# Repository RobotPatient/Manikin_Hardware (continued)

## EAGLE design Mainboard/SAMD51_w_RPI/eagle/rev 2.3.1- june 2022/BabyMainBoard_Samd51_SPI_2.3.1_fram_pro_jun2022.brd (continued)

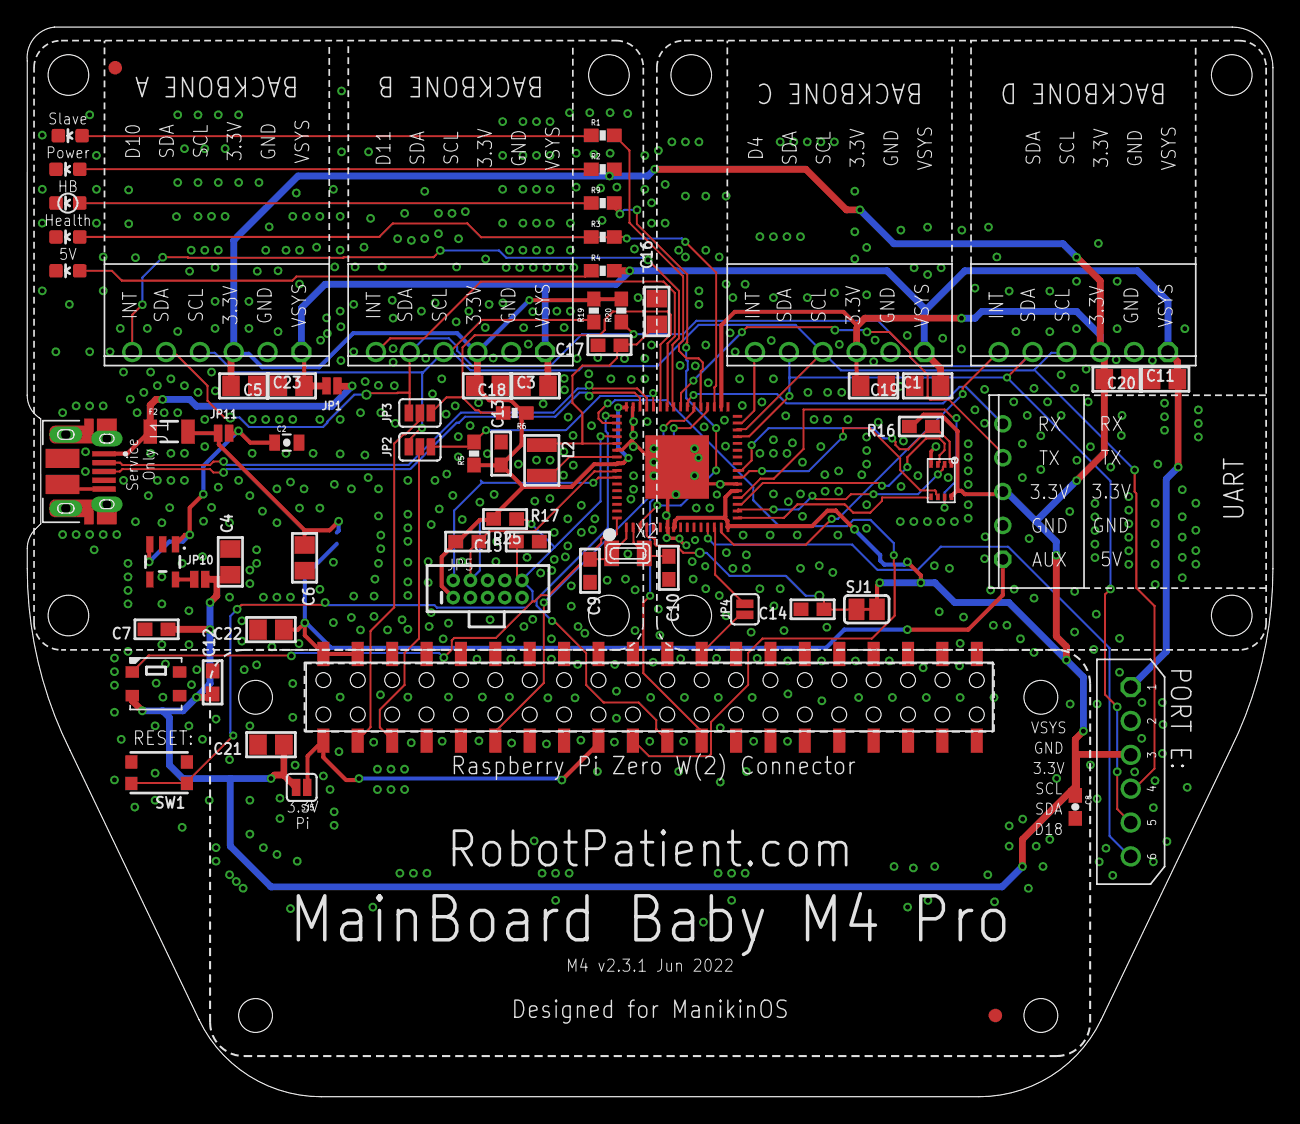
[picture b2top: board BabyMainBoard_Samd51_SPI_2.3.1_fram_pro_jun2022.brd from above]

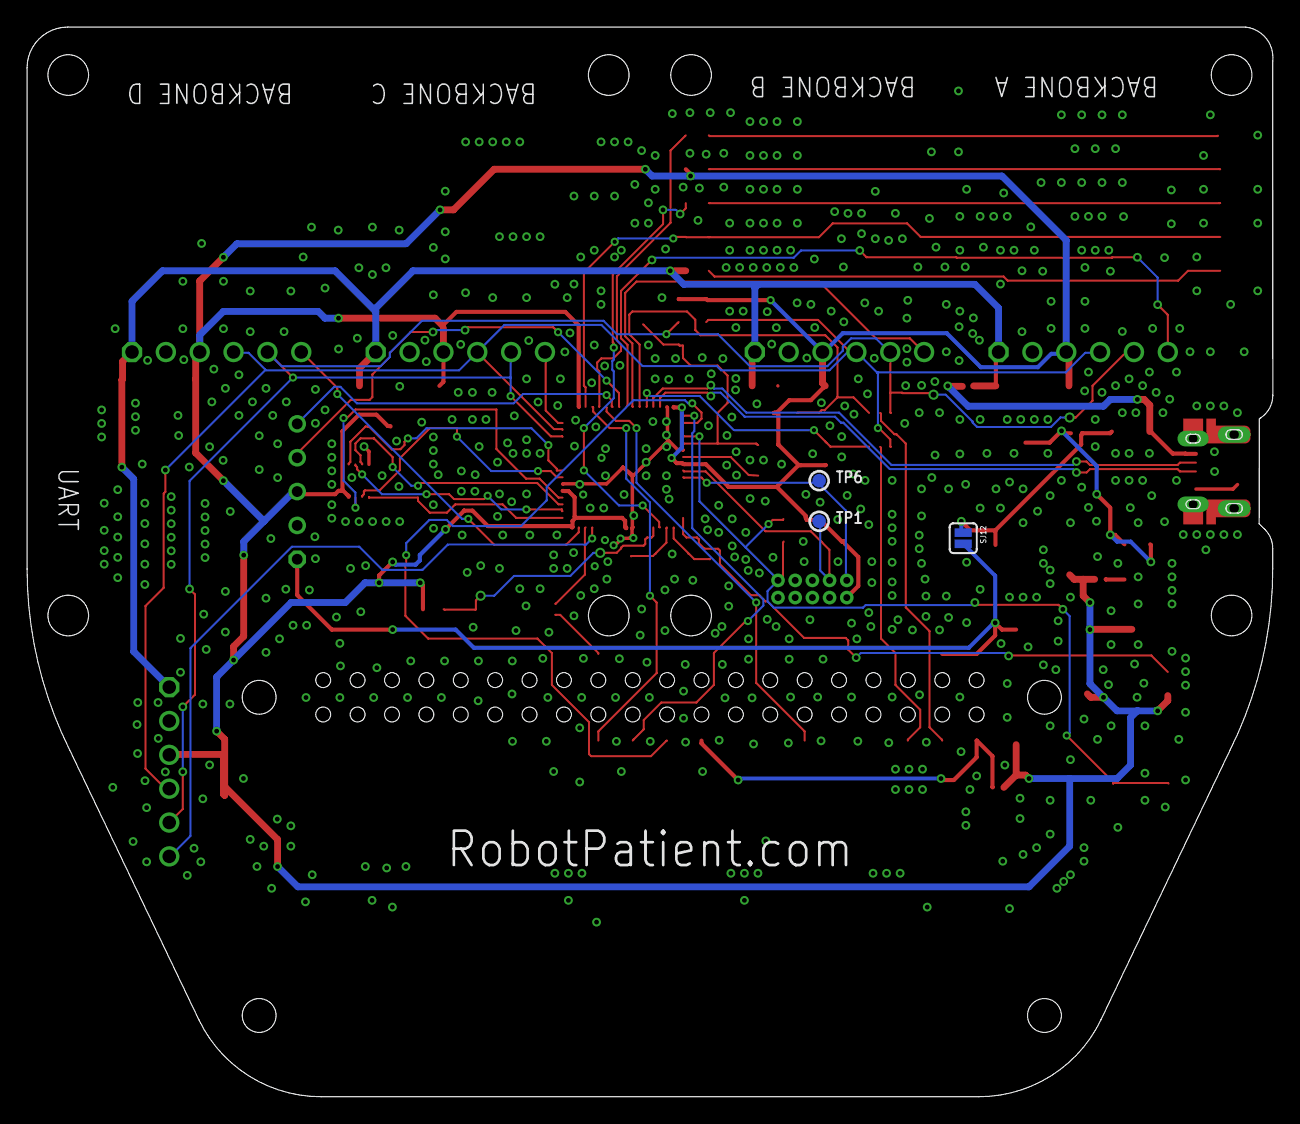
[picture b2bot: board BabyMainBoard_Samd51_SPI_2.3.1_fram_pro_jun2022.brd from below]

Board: 2 copper layers, 92.0 x 79.0 mm, 72 parts (3 on the bottom side), 52 nets.

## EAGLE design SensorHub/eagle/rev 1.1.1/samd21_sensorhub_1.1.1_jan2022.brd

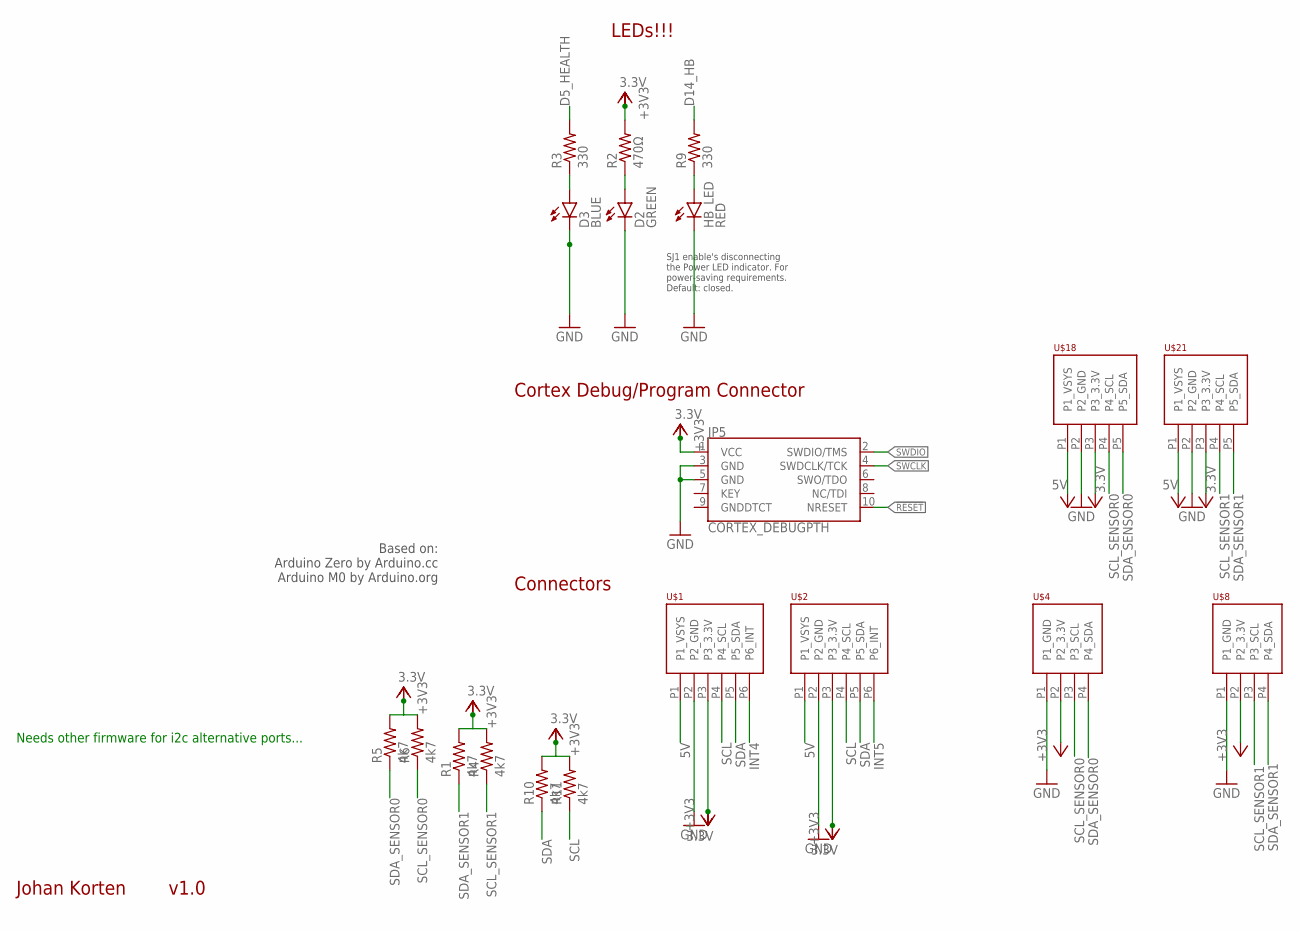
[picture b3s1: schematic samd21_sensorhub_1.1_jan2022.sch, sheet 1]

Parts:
D2: GREEN; LED-0603
D3: BLUE; LED-0603
HB_LED: RED; LED-0603
JP5: CORTEX_DEBUGPTH; 2X5-PTH-1.27MM
R1, R4, R5, R6, R10, R11: 4k7; 0603-RES
R2: 470Ω; 0603-RES
R3, R9: 330; 0603-RES
U$1, U$2: PHOENIX_PTSM_M6_TH_I2CPPANGLE; PTSM_M6_THRHOLE
U$4, U$8: PHOENIX_PTSM_M4_THANGLE; PTSM_M4_TH
U$18, U$21: PHOENIX_PTSM_M5_TH_I2C++; PTSM_M5_THRHOLE

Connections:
3.3V: JP5.1 (VCC), R1.2, R2.2, R4.2, R5.2, R6.2, R10.2, R11.2, U$1.P3 (P3_3.3V), U$2.P3 (P3_3.3V), U$4.P2 (P2_3.3V), U$8.P2 (P2_3.3V), U$18.P3 (P3_3.3V), U$21.P3 (P3_3.3V); also elsewhere on the board
5V: U$1.P1 (P1_VSYS), U$2.P1 (P1_VSYS), U$18.P1 (P1_VSYS), U$21.P1 (P1_VSYS); also elsewhere on the board
!RESET: JP5.10 (NRESET); also elsewhere on the board
D5_HEALTH: R3.2; also elsewhere on the board
D5_HEALTH_LED: D3.A, R3.1
D14_HB: R9.2; also elsewhere on the board
D14_HB_LED: HB_LED.A, R9.1
GND: D2.C, D3.C, HB_LED.C, JP5.3 (GND), JP5.5 (GND), U$1.P2 (P2_GND), U$2.P2 (P2_GND), U$4.P1 (P1_GND), U$8.P1 (P1_GND), U$18.P2 (P2_GND), U$21.P2 (P2_GND); also elsewhere on the board
INT4: U$1.P6 (P6_INT); also elsewhere on the board
INT5: U$2.P6 (P6_INT); also elsewhere on the board
unnamed: D2.A, R2.1
SCL: R11.1, U$1.P4 (P4_SCL), U$2.P4 (P4_SCL); also elsewhere on the board
SCL_SENSOR0: R6.1, U$4.P3 (P3_SCL), U$18.P4 (P4_SCL); also elsewhere on the board
SCL_SENSOR1: R4.1, U$8.P3 (P3_SCL), U$21.P4 (P4_SCL); also elsewhere on the board
SDA: R10.1, U$1.P5 (P5_SDA), U$2.P5 (P5_SDA); also elsewhere on the board
SDA_SENSOR0: R5.1, U$4.P4 (P4_SDA), U$18.P5 (P5_SDA); also elsewhere on the board
SDA_SENSOR1: R1.1, U$8.P4 (P4_SDA), U$21.P5 (P5_SDA); also elsewhere on the board
SWCLK: JP5.4 (SWDCLK/TCK); also elsewhere on the board
SWDIO: JP5.2 (SWDIO/TMS); also elsewhere on the board

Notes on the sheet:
LEDs!!!
Cortex Debug/Program Connector
Connectors
Johan Korten
v1.0
SJ1 enable's disconnecting the Power LED indicator. For power-saving requirements. Default: closed.
Based on: Arduino Zero by Arduino.cc Arduino M0 by Arduino.org
Needs other firmware for i2c alternative ports...

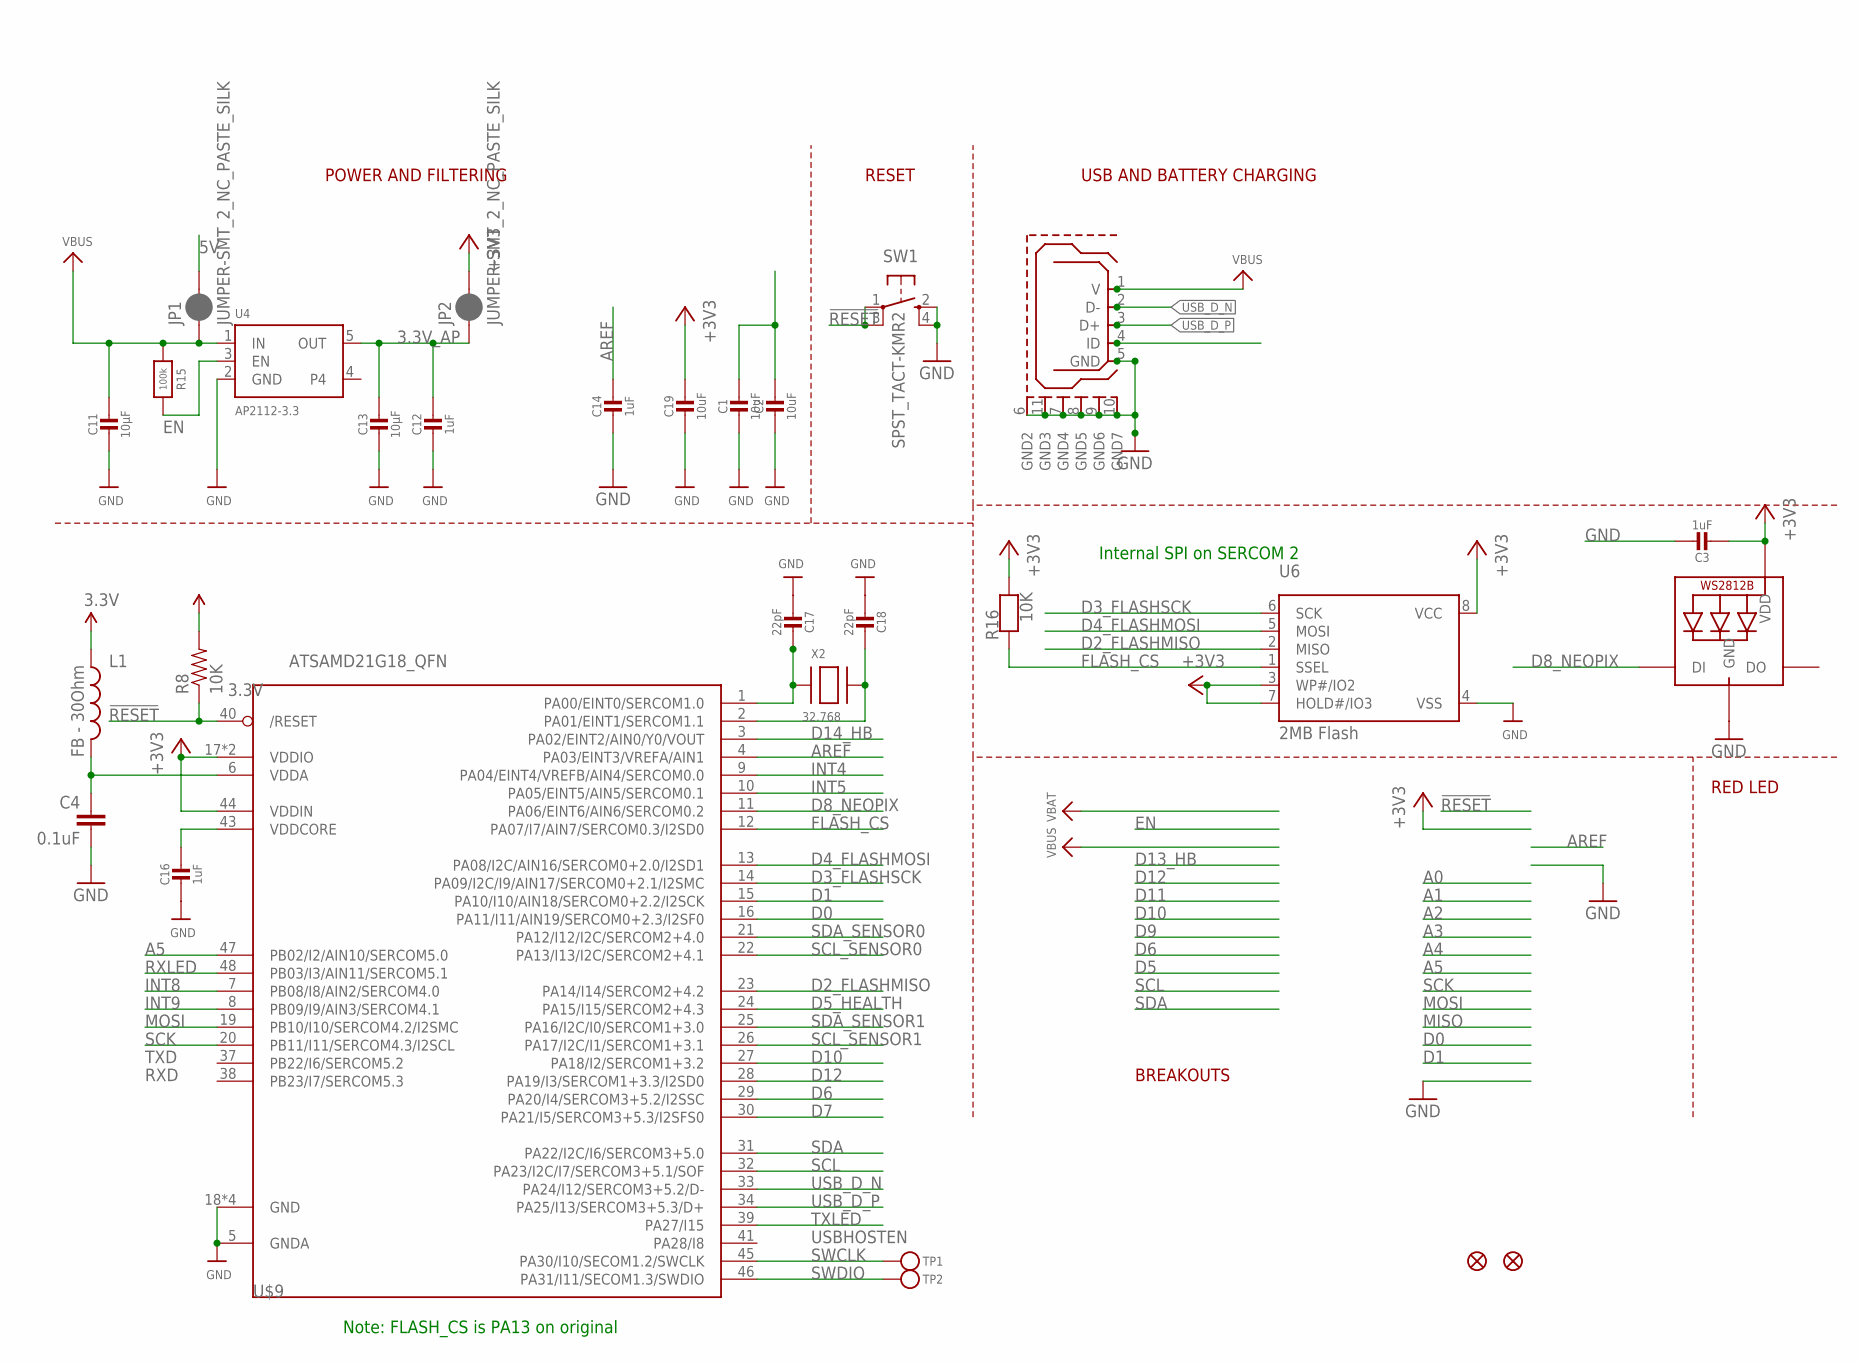
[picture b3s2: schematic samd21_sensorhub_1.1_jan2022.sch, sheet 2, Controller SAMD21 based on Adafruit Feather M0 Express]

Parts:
C1, C2, C19: 10uF; 0805-NO
C3, C12, C14, C16: 1uF; 0603-NO
C4: 0.1uF; 0402-CAP
C11, C13: 10µF; 0805-NO
C17, C18: 22pF; 0603-NO
JP1, JP2: JUMPER-SMT_2_NC_PASTE_SILK; SMT-JUMPER_2_NC_PASTE_SILK
L1: FB - 30Ohm; 0603
LED1: WS2812B3535; LED3535
R8: 10K; 0603-RES
R15: 100k; 0603-NO
R16: 10K; 0603-NO
SW1: SPST_TACT-KMR2; KMR2
TP1, TP2: TESTPOINTROUND1.5MM; TESTPOINT_ROUND_1.5MM
U4: AP2112-3.3; SOT23-5
U6: 2MB Flash; SOIC8_208MIL
U$6: USB_MICROB; USB_MICROB_PACKAGE
U$9: ATSAMD21G18_QFN; TQFN48_7MM
U$34, U$35: FIDUCIAL""; FIDUCIAL_1MM
X2: 32.768; XTAL3215

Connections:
3.3V: C3.2, C19.1, JP2.2, L1.1, LED1.2 (VDD), R8.2, R16.2, U6.3 (WP#/IO2), U6.7 (HOLD#/IO3), U6.8 (VCC), U$9.17 (VDDIO), U$9.36 (VDDIO), U$9.44 (VDDIN); also elsewhere on the board
3.3V_AP: C12.1, C13.1, JP2.1, U4.5 (OUT)
5V: C1.1, C2.1, JP1.2; also elsewhere on the board
!RESET: R8.1, SW1.1, SW1.3 (P1), U$9.40 (/RESET); also elsewhere on the board
A5: U$9.47 (PB02/I2/AIN10/SERCOM5.0)
AREF: C14.1, U$9.4 (PA03/EINT3/VREFA/AIN1)
D0: U$9.16 (PA11/I11/AIN19/SERCOM0+2.3/I2SF0)
D1: U$9.15 (PA10/I10/AIN18/SERCOM0+2.2/I2SCK)
D2_FLASHMISO: U6.2 (MISO), U$9.23 (PA14/I14/SERCOM2+4.2)
D3_FLASHSCK: U6.6 (SCK), U$9.14 (PA09/I2C/I9/AIN17/SERCOM0+2.1/I2SMC)
D4_FLASHMOSI: U6.5 (MOSI), U$9.13 (PA08/I2C/AIN16/SERCOM0+2.0/I2SD1)
D5_HEALTH: U$9.24 (PA15/I15/SERCOM2+4.3); also elsewhere on the board
D6: U$9.29 (PA20/I4/SERCOM3+5.2/I2SSC)
D7: U$9.30 (PA21/I5/SERCOM3+5.3/I2SFS0)
D8_NEOPIX: LED1.1 (DI), U$9.11 (PA06/EINT6/AIN6/SERCOM0.2)
D10: U$9.27 (PA18/I2/SERCOM1+3.2)
D12: U$9.28 (PA19/I3/SERCOM1+3.3/I2SD0)
D14_HB: U$9.3 (PA02/EINT2/AIN0/Y0/VOUT); also elsewhere on the board
EN: R15.2, U4.3 (EN)
FLASH_CS: R16.1, U6.1 (SSEL), U$9.12 (PA07/I7/AIN7/SERCOM0.3/I2SD0)
GND: C1.2, C2.2, C3.1, C4.2, C11.2, C12.2, C13.2, C14.2, C16.2, C17.2, C18.2, C19.2, LED1.4 (GND), SW1.2 (S), SW1.4 (S1), U4.2 (GND), U6.4 (VSS), U$6.5 (GND), U$6.6 (GND2), U$6.7 (GND4), U$6.8 (GND5), U$6.9 (GND6), U$6.10 (GND7), U$6.11 (GND3), U$9.5 (GNDA), U$9.18 (GND), U$9.35 (GND), U$9.42 (GND), U$9.THERMAL (GND); also elsewhere on the board
INT4: U$9.9 (PA04/EINT4/VREFB/AIN4/SERCOM0.0); also elsewhere on the board
INT5: U$9.10 (PA05/EINT5/AIN5/SERCOM0.1); also elsewhere on the board
INT8: U$9.7 (PB08/I8/AIN2/SERCOM4.0)
INT9: U$9.8 (PB09/I9/AIN3/SERCOM4.1)
MOSI: U$9.19 (PB10/I10/SERCOM4.2/I2SMC)
unnamed: C17.1, U$9.1 (PA00/EINT0/SERCOM1.0), X2.P$1
unnamed: C18.1, U$9.2 (PA01/EINT1/SERCOM1.1), X2.P$2
RXLED: U$9.48 (PB03/I3/AIN11/SERCOM5.1)
SCK: U$9.20 (PB11/I11/SERCOM4.3/I2SCL)
SCL: U$9.32 (PA23/I2C/I7/SERCOM3+5.1/SOF); also elsewhere on the board
SCL_SENSOR0: U$9.22 (PA13/I13/I2C/SERCOM2+4.1); also elsewhere on the board
SCL_SENSOR1: U$9.26 (PA17/I2C/I1/SERCOM1+3.1); also elsewhere on the board
SDA: U$9.31 (PA22/I2C/I6/SERCOM3+5.0); also elsewhere on the board
SDA_SENSOR0: U$9.21 (PA12/I12/I2C/SERCOM2+4.0); also elsewhere on the board
SDA_SENSOR1: U$9.25 (PA16/I2C/I0/SERCOM1+3.0); also elsewhere on the board
SWCLK: TP1.P$1, U$9.45 (PA30/I10/SECOM1.2/SWCLK); also elsewhere on the board
SWDIO: TP2.P$1, U$9.46 (PA31/I11/SECOM1.3/SWDIO); also elsewhere on the board
TXLED: U$9.39 (PA27/I15)
USB_D_N: U$6.2 (D-), U$9.33 (PA24/I12/SERCOM3+5.2/D-); also elsewhere on the board
USB_D_P: U$6.3 (D+), U$9.34 (PA25/I13/SERCOM3+5.3/D+); also elsewhere on the board
VBUS: C11.1, JP1.1, R15.1, U4.1 (IN), U$6.1 (V); also elsewhere on the board
VDDANA: C4.1, L1.2, U$9.6 (VDDA)
VDDCORE1: C16.1, U$9.43 (VDDCORE)

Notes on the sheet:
POWER AND FILTERING
RESET
USBHOSTEN
TXD
RXD
USB AND BATTERY CHARGING
BREAKOUTS
RED LED
Internal SPI on SERCOM 2
Note: FLASH_CS is PA13 on original

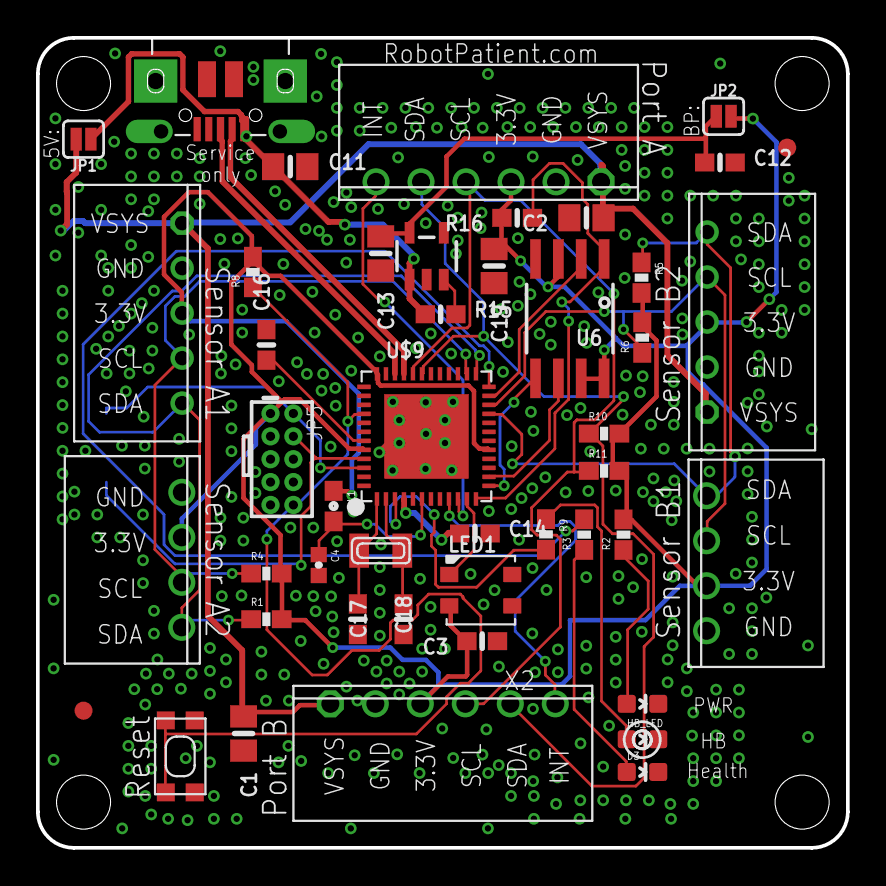
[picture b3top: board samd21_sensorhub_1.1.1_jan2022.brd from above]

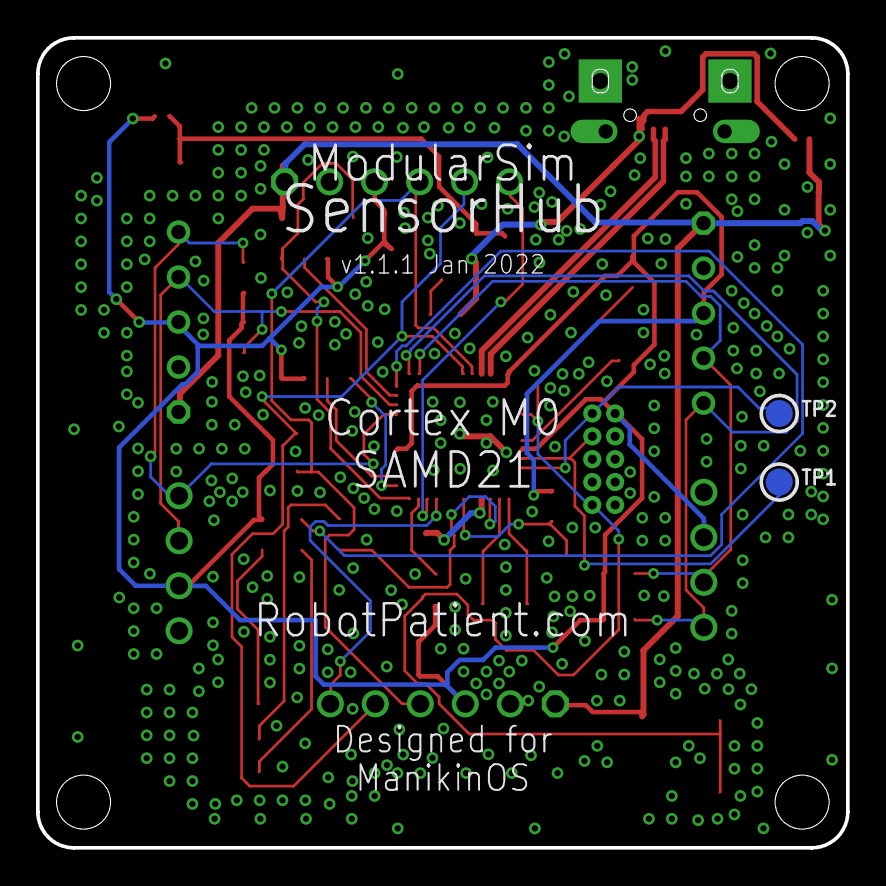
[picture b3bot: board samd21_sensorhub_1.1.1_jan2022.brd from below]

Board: 2 copper layers, 45.0 x 45.0 mm, 48 parts (2 on the bottom side), 34 nets.

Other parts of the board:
X3: microUSB; 4UCONN_20329_V2

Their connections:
GND: X3.BASE@1, X3.BASE@2, X3.GND, X3.SPRT@1, X3.SPRT@2, X3.SPRT@3, X3.SPRT@4; also elsewhere on the board
USB_D_N: X3.D-; also elsewhere on the board
USB_D_P: X3.D+; also elsewhere on the board
VBUS: X3.VBUS; also elsewhere on the board

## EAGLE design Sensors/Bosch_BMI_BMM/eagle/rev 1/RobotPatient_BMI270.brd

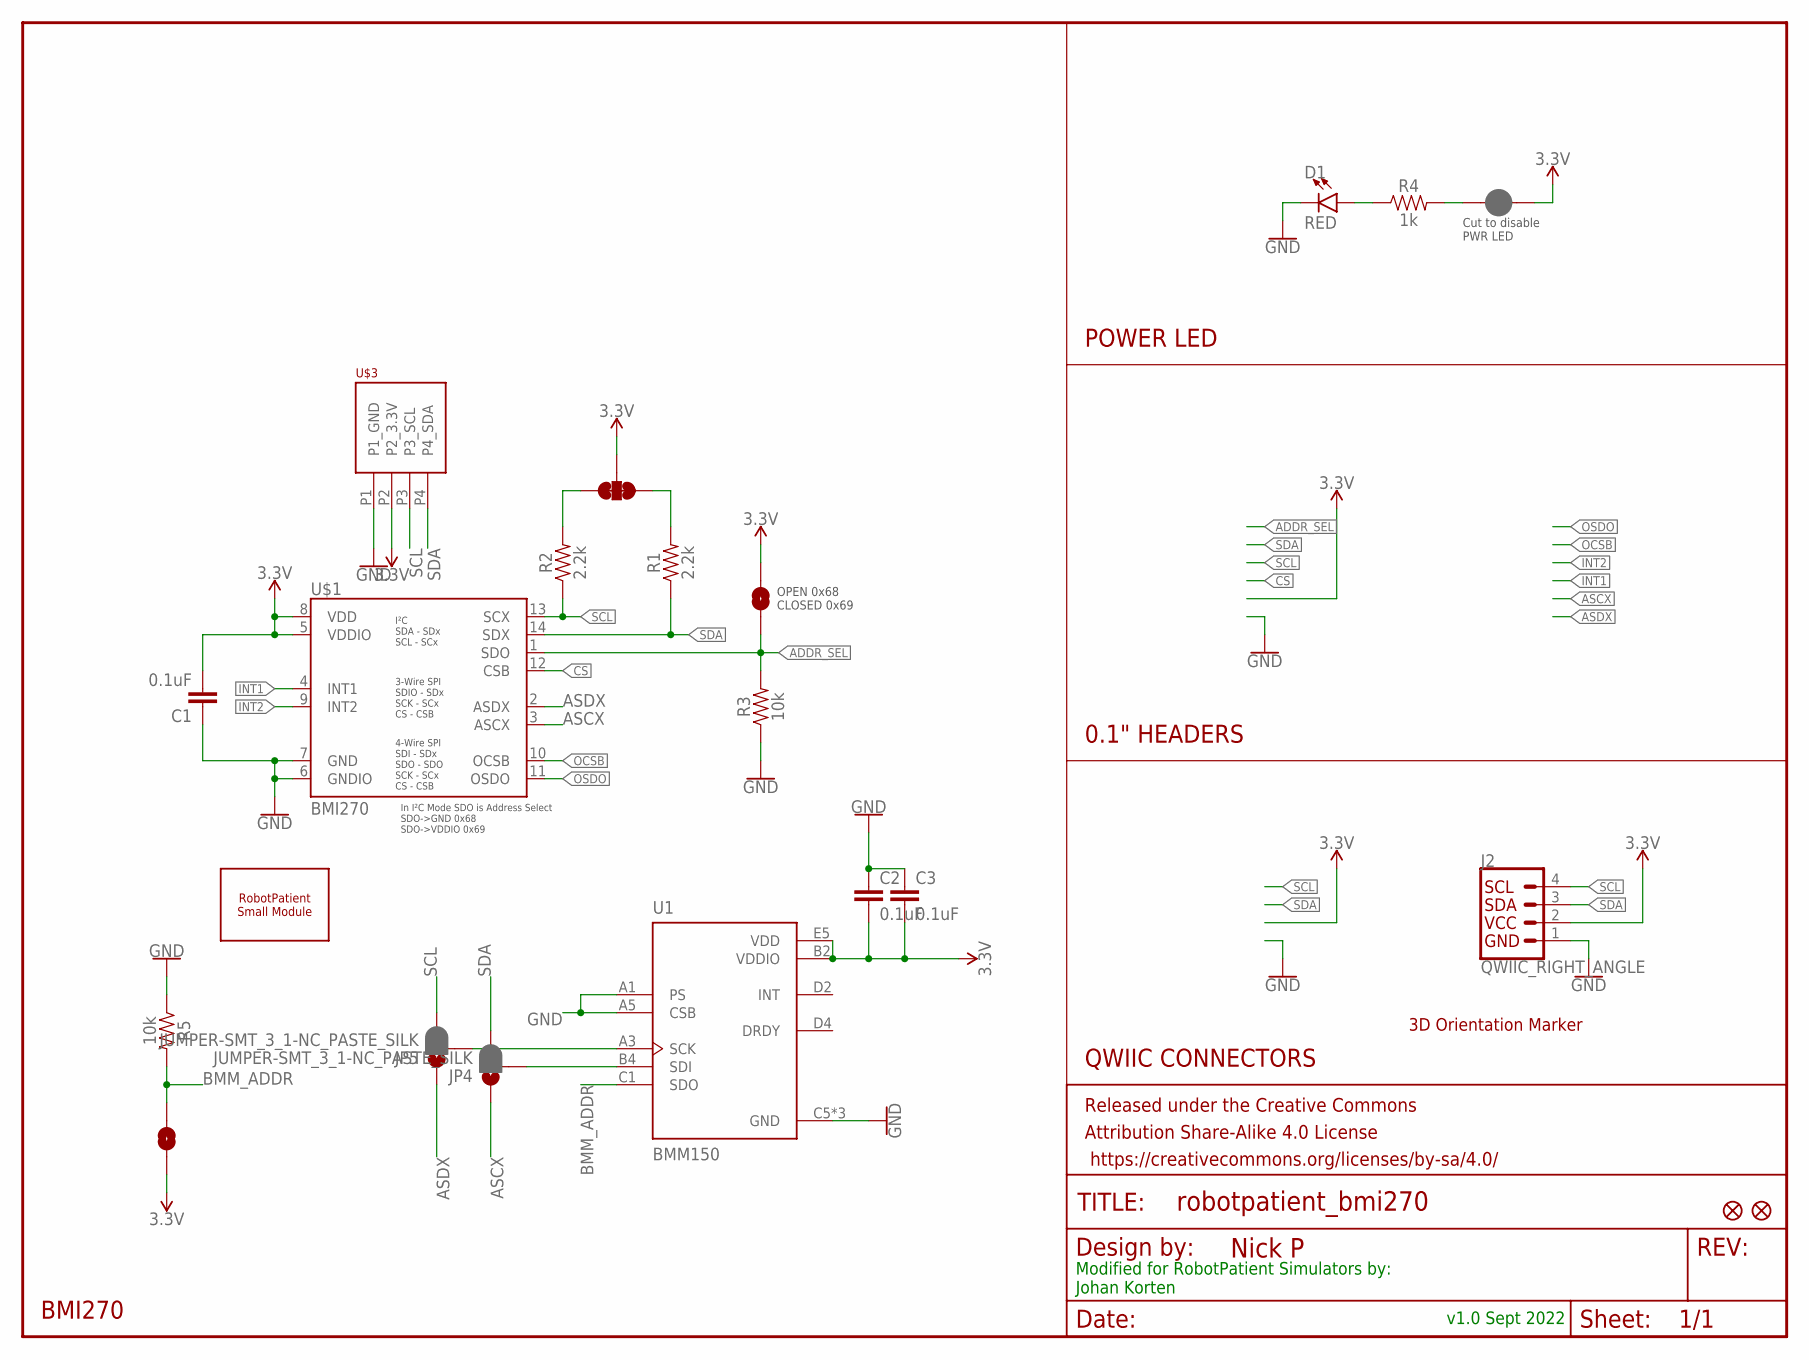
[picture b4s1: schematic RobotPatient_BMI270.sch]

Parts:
C1, C2, C3: 0.1uF; 0603
D1: RED; LED-0603
FD1, FD2: FIDUCIAL1X2; FIDUCIAL-1X2
FRAME1: FRAME-LETTERNO_PACKAGE; DUMMY
J2: QWIIC_RIGHT_ANGLE; JST04_1MM_RA
JP1: JUMPER-SMT_3_2-NC_TRACE_SILK; SMT-JUMPER_3_2-NC_TRACE_SILK
JP2, JP6: JUMPER-SMT_2_NO_SILK; SMT-JUMPER_2_NO_SILK
JP3: JUMPER-SMT_2_NC_PASTE_SILK; SMT-JUMPER_2_NC_PASTE_SILK
JP4, JP5: JUMPER-SMT_3_1-NC_PASTE_SILK; SMT-JUMPER_3_1-NC_PASTE_SILK
R1, R2: 2.2k; 0603
R3, R5: 10k; 0603
R4: 1k; 0603
U1: BMM150; XDCR_BMM150
U$1: BMI270
U$2: 3D_MARKER
U$3: PHOENIX_PTSM_M4_THANGLE; PTSM_M4_TH
U$40: ROBOTPATIENT_SMALL_MODULEBOARD; RP_SMALL_SENSOR_OUTLINE

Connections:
3.3V: C1.2, C2.2, C3.2, J2.2, JP1.2, JP2.2, JP3.2, JP6.2, U1.B2 (VDDIO), U1.E5 (VDD), U$1.5 (VDDIO), U$1.8 (VDD), U$3.P2 (P2_3.3V)
ADDR_SEL: JP2.1, R3.2, U$1.1 (SDO)
ASCX: JP4.1, U$1.3 (ASCX)
ASDX: JP5.1, U$1.2 (ASDX)
BMM_ADDR: JP6.1, R5.2, U1.C1 (SDO)
CS: U$1.12 (CSB)
GND: C1.1, C2.1, C3.1, D1.C, J2.1, R3.1, R5.1, U1.A1 (PS), U1.A5 (CSB), U1.C5 (GND), U1.E1 (GND), U1.E3 (GND), U$1.6 (GNDIO), U$1.7 (GND), U$3.P1 (P1_GND)
INT1: U$1.4 (INT1)
INT2: U$1.9 (INT2)
unnamed: JP1.1, R1.2
unnamed: JP1.3, R2.2
unnamed: JP3.1, R4.2
unnamed: D1.A, R4.1
unnamed: JP4.2, U1.B4 (SDI)
unnamed: JP5.2, U1.A3 (SCK)
OCSB: U$1.10 (OCSB)
OSDO: U$1.11 (OSDO)
SCL: J2.4, JP5.3, R2.1, U$1.13 (SCX), U$3.P3 (P3_SCL)
SDA: J2.3, JP4.3, R1.1, U$1.14 (SDX), U$3.P4 (P4_SDA)

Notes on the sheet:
OPEN 0x68 CLOSED 0x69
BMI270
Cut to disable PWR LED
POWER LED
0.1" HEADERS
QWIIC CONNECTORS
Modified for RobotPatient Simulators by: Johan Korten

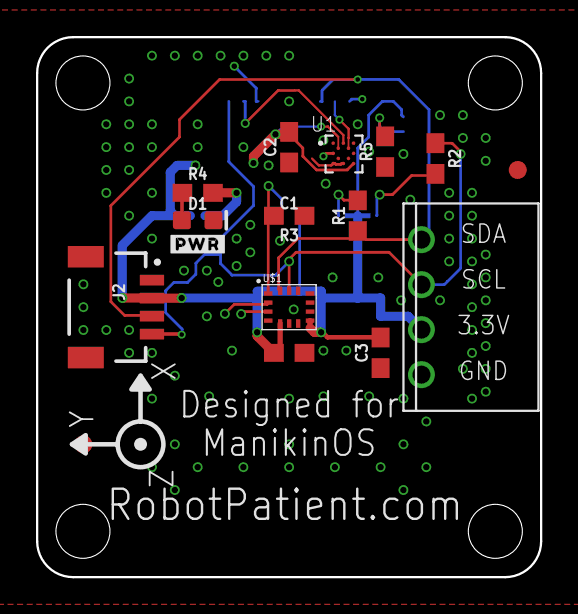
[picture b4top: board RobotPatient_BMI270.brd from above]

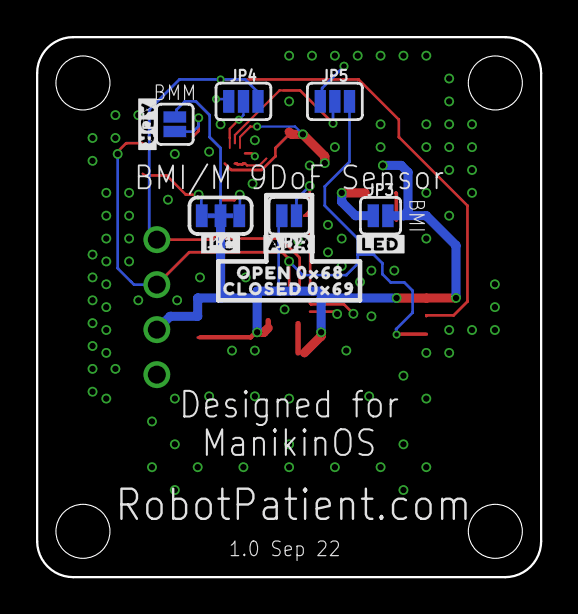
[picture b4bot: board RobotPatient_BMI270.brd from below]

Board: 4 copper layers, 28.0 x 30.0 mm, 31 parts (12 on the bottom side), 14 nets.

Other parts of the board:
U$4, U$23: #ADR#2713
U$18: #PWR#2711
U$21: #I�C#2714
U$22: #LED#2712
U$24: OPEN_0X682714
U$25: CLOSED_0X692714

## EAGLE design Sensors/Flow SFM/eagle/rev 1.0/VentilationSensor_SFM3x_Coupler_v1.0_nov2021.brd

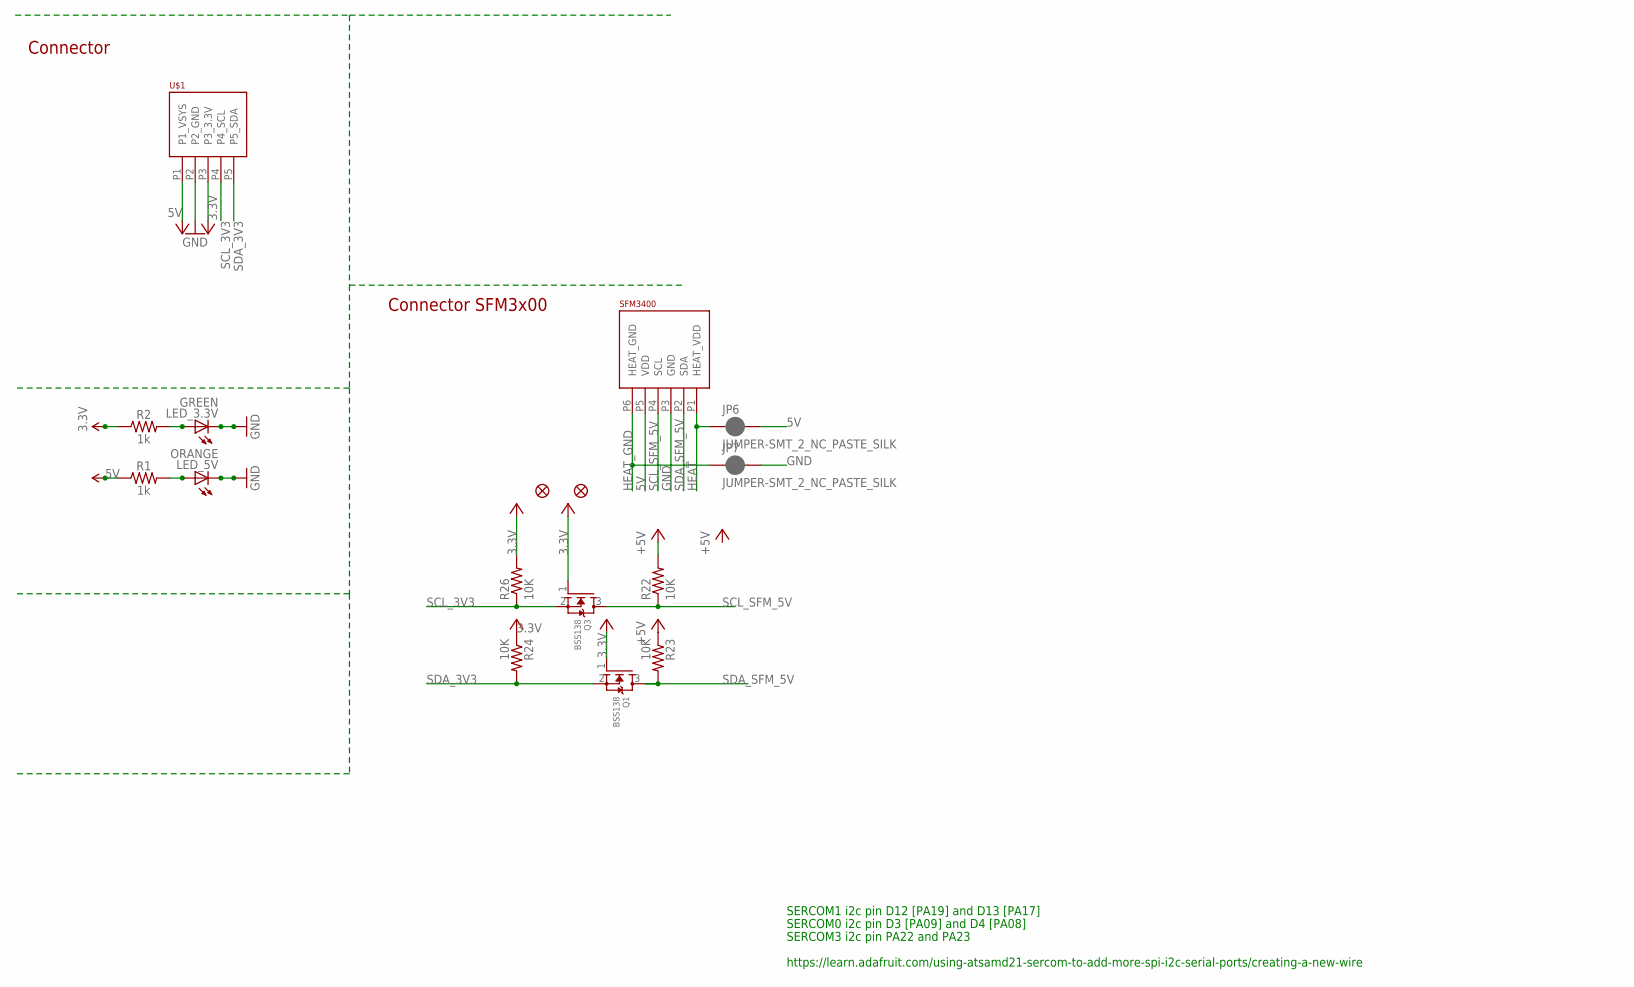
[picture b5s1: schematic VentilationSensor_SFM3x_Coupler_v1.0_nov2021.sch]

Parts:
FD1, FD2: FIDUCIAL1X2; FIDUCIAL-1X2
JP6, JP7: JUMPER-SMT_2_NC_PASTE_SILK; SMT-JUMPER_2_NC_PASTE_SILK
LED_3.3V: GREEN; LED-0603
LED_5V: ORANGE; LED-0603
Q1, Q3: BSS138; SOT23
R1, R2: 1k; 0603
R22, R23, R24, R26: 10K; R0805
SFM3400: SFMXX00
U$1: PHOENIX_PTSM_M5_TH_I2C++; PTSM_M5_THRHOLE

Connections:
3.3V: Q1.1 (G), Q3.1 (G), R2.1, R24.1, R26.2, U$1.P3 (P3_3.3V)
5V: JP6.2, R1.1, R22.2, R23.1, SFM3400.P5 (VDD), U$1.P1 (P1_VSYS)
GND: JP7.2, LED_3.3V.C, LED_5V.C, SFM3400.P3 (GND), U$1.P2 (P2_GND)
HEAT: JP6.1, SFM3400.P1 (HEAT_VDD)
HEAT_GND: JP7.1, SFM3400.P6 (HEAT_GND)
unnamed: LED_5V.A, R1.2
unnamed: LED_3.3V.A, R2.2
SCL_3V3: Q3.2 (S), R26.1, U$1.P4 (P4_SCL)
SCL_SFM_5V: Q3.3 (D), R22.1, SFM3400.P4 (SCL)
SDA_3V3: Q1.2 (S), R24.2, U$1.P5 (P5_SDA)
SDA_SFM_5V: Q1.3 (D), R23.2, SFM3400.P2 (SDA)

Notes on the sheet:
SERCOM1 i2c pin D12 [PA19] and D13 [PA17]
https://learn.adafruit.com/using-atsamd21-sercom-to-add-more-spi-i2c-serial-ports/creating-a-new-wire
SERCOM0 i2c pin D3 [PA09] and D4 [PA08]
SERCOM3 i2c pin PA22 and PA23
Connector SFM3x00
Connector

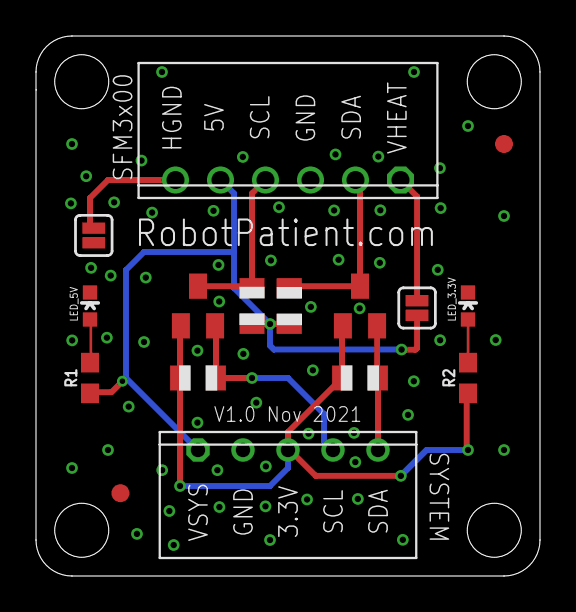
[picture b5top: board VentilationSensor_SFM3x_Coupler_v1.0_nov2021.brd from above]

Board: 2 copper layers, 28.0 x 30.0 mm, 16 parts (0 on the bottom side), 11 nets.

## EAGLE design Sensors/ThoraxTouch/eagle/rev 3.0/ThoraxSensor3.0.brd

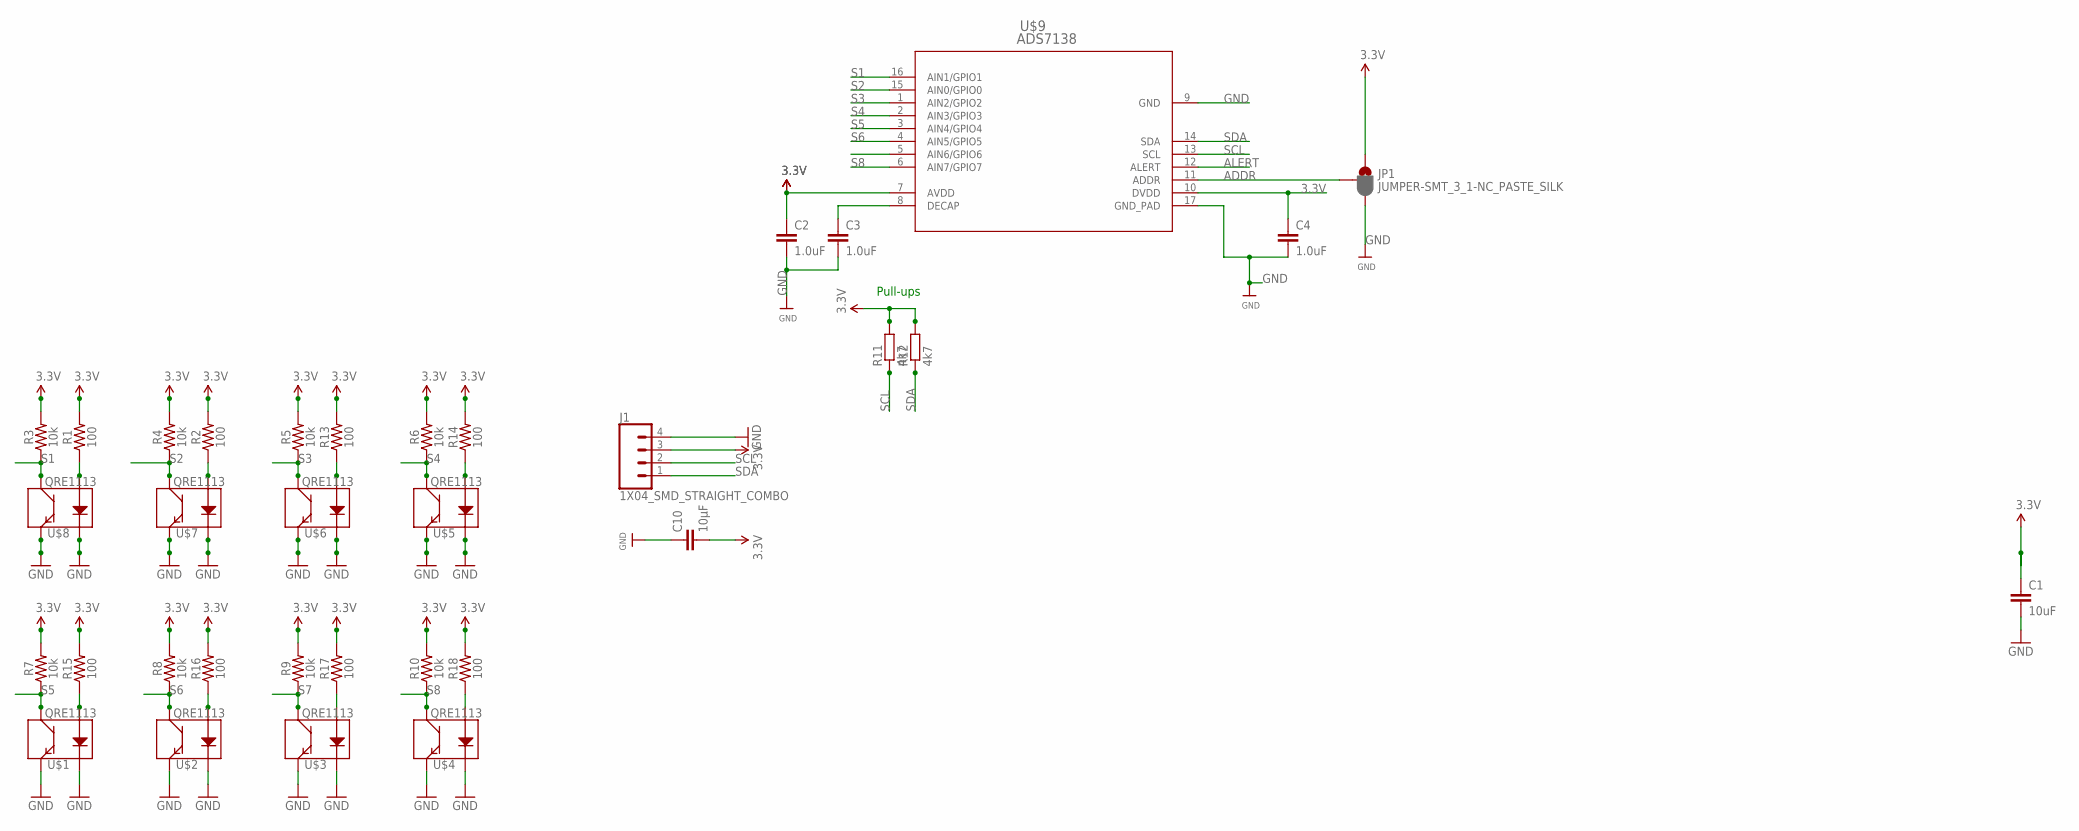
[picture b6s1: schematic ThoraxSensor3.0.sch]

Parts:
C1: 10uF; 0805
C2, C3, C4: 1.0uF; 0603
C10: 10µF; C0805
J1: 1X04_SMD_STRAIGHT_COMBO; 1X04_SMD_VERTICAL_COMBO
JP1: JUMPER-SMT_3_1-NC_PASTE_SILK; SMT-JUMPER_3_1-NC_PASTE_SILK
R1, R2, R13, R14, R15, R16, R17, R18: 100; 0603
R3, R4, R5, R6, R7, R8, R9, R10: 10k; 0603
R11, R12: 4k7; R0603
U$1, U$2, U$3, U$4, U$5, U$6, U$7, U$8: QRE1113
U$9: ADS7138; QFN_8IRTER_TEX

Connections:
3.3V: C1.1, C2.1, C4.1, C10.2, J1.3, JP1.1, R1.2, R2.2, R3.2, R4.2, R5.2, R6.2, R7.2, R8.2, R9.2, R10.2, R11.2, R12.2, R13.2, R14.2, R15.2, R16.2, R17.2, R18.2, U$9.7 (AVDD), U$9.10 (DVDD)
ADDR: JP1.2, U$9.11 (ADDR)
ALERT: U$9.12 (ALERT)
GND: C1.2, C2.2, C3.2, C4.2, C10.1, J1.4, JP1.3, U$1.2 (K), U$1.4 (E), U$2.2 (K), U$2.4 (E), U$3.2 (K), U$3.4 (E), U$4.2 (K), U$4.4 (E), U$5.2 (K), U$5.4 (E), U$6.2 (K), U$6.4 (E), U$7.2 (K), U$7.4 (E), U$8.2 (K), U$8.4 (E), U$9.9 (GND), U$9.17 (GND_PAD)
unnamed: R1.1, U$8.1 (A)
unnamed: R2.1, U$7.1 (A)
unnamed: R13.1, U$6.1 (A)
unnamed: R14.1, U$5.1 (A)
unnamed: R15.1, U$1.1 (A)
unnamed: R16.1, U$2.1 (A)
unnamed: R17.1, U$3.1 (A)
unnamed: R18.1, U$4.1 (A)
unnamed: C3.1, U$9.8 (DECAP)
S1: R3.1, U$8.3 (C), U$9.16 (AIN1/GPIO1)
S2: R4.1, U$7.3 (C), U$9.15 (AIN0/GPIO0)
S3: R5.1, U$6.3 (C), U$9.1 (AIN2/GPIO2)
S4: R6.1, U$5.3 (C), U$9.2 (AIN3/GPIO3)
S5: R7.1, U$1.3 (C), U$9.3 (AIN4/GPIO4)
S6: R8.1, U$2.3 (C), U$9.4 (AIN5/GPIO5)
S7: R9.1, U$3.3 (C), U$9.5 (AIN6/GPIO6)
S8: R10.1, U$4.3 (C), U$9.6 (AIN7/GPIO7)
SCL: J1.2, R11.1, U$9.13 (SCL)
SDA: J1.1, R12.1, U$9.14 (SDA)

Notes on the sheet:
Pull-ups

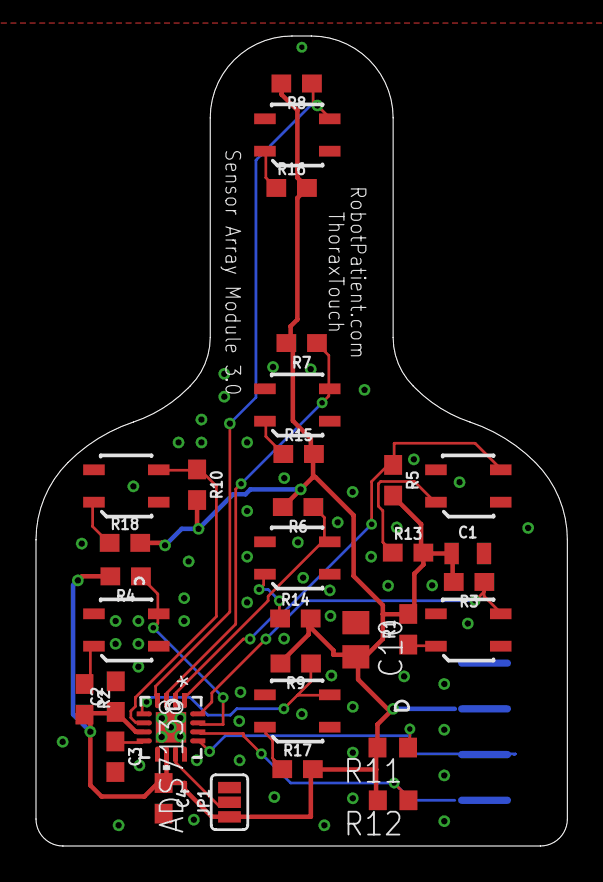
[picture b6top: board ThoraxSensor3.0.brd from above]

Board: 2 copper layers, 29.5 x 45.0 mm, 34 parts (1 on the bottom side), 22 nets.
